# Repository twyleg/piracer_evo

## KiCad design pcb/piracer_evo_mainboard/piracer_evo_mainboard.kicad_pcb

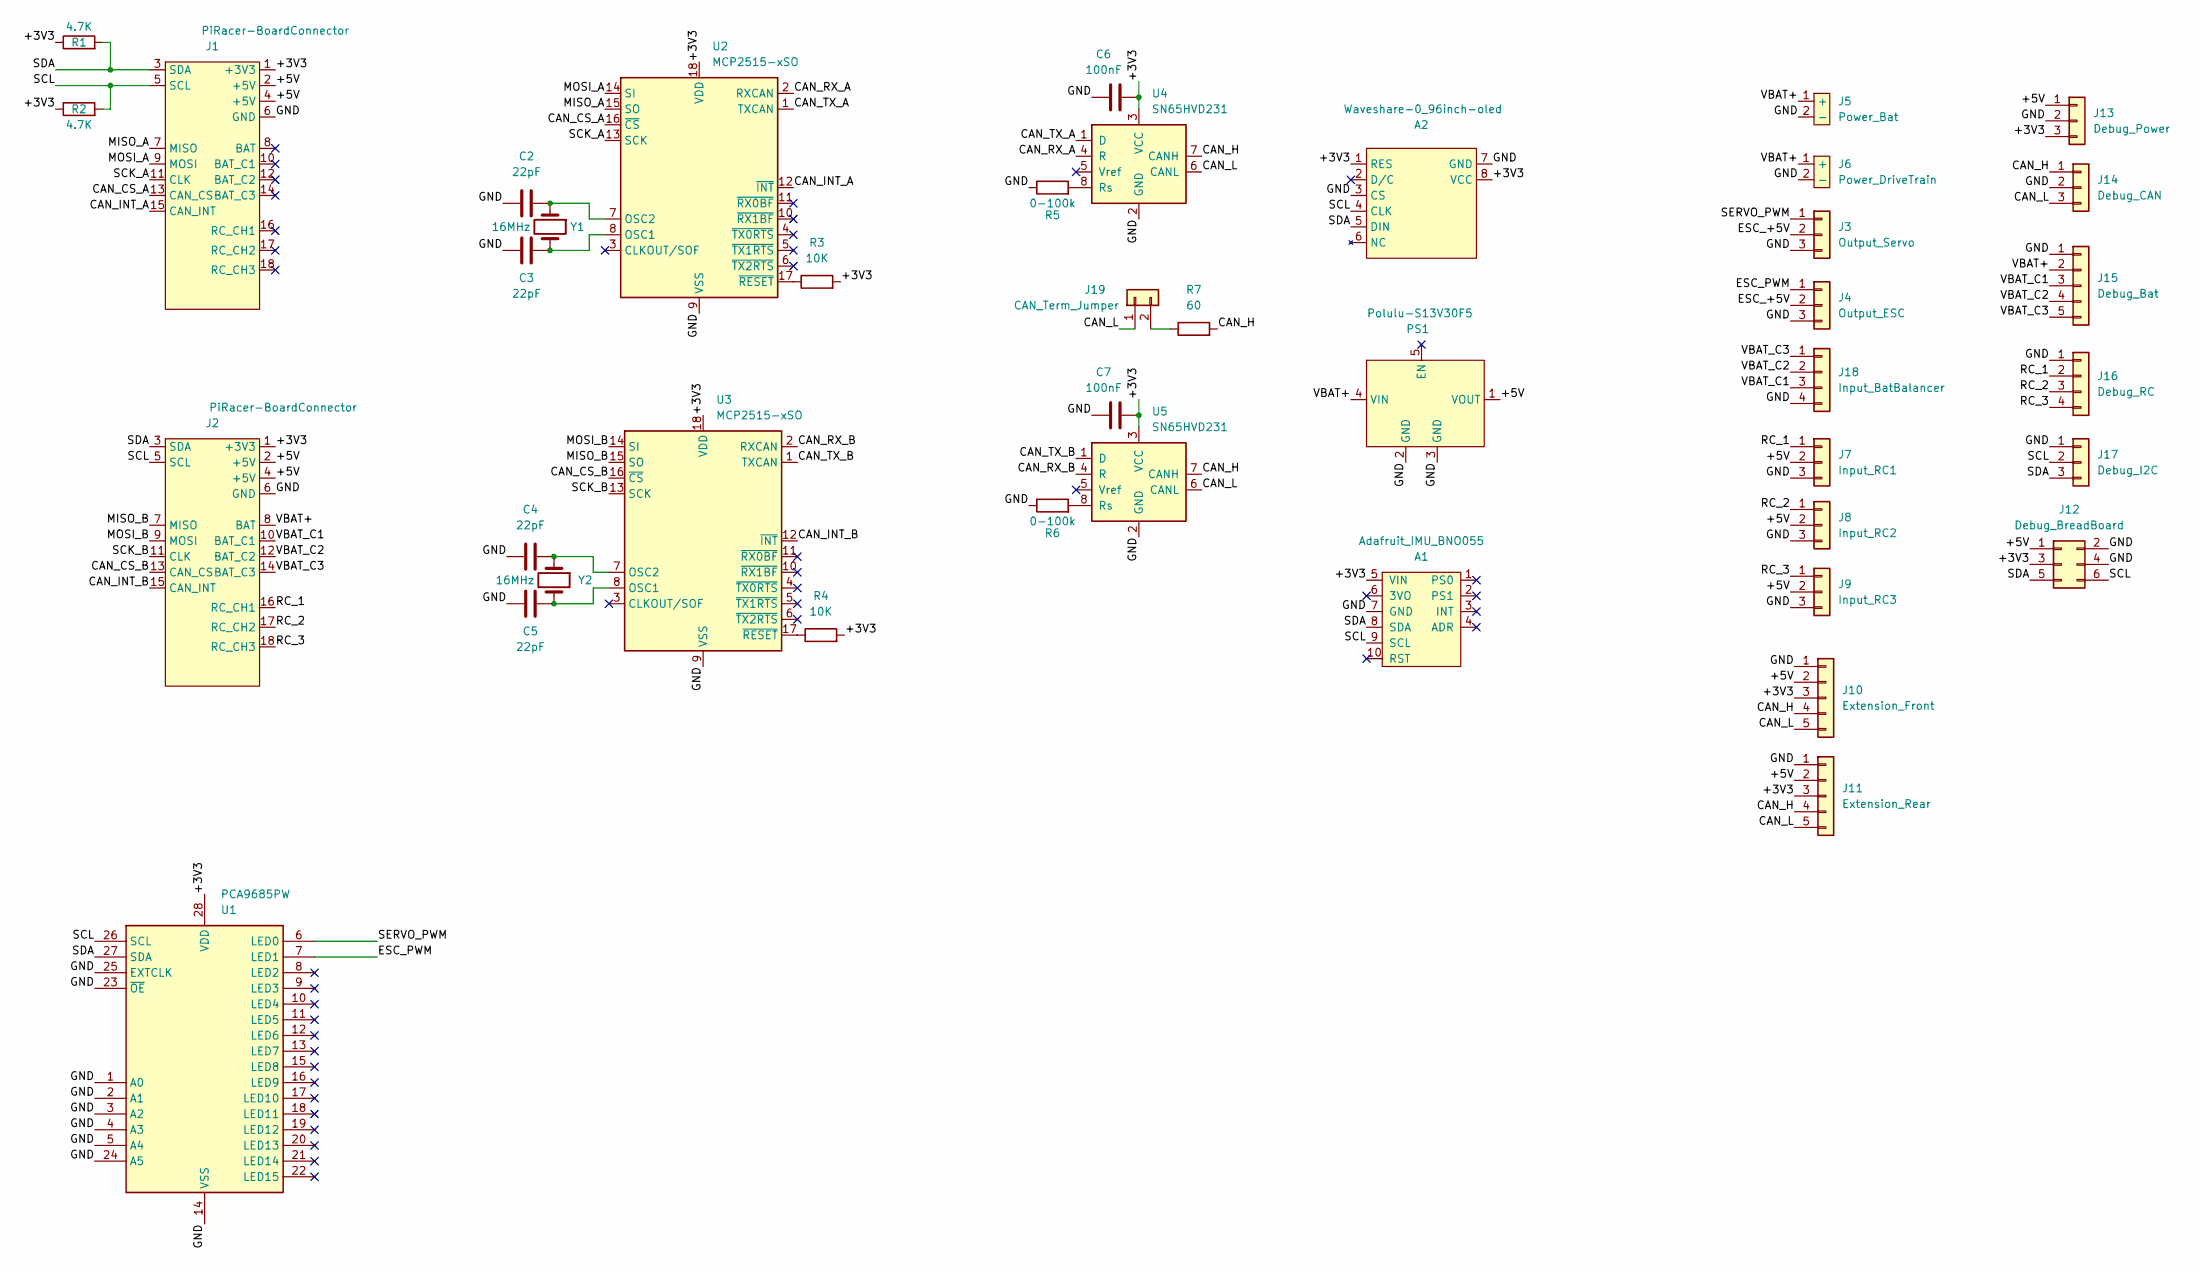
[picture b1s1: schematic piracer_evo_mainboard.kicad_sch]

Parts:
A1: Adafruit_IMU_BNO055
A2: Waveshare-0_96inch-oled
C2, C3, C4, C5: 22pF; C_0805_2012Metric_Pad1.18x1.45mm_HandSolder
C6, C7: 100nF; C_0805_2012Metric_Pad1.18x1.45mm_HandSolder
J1: PiRacer-BoardConnector; RaspberryPi3-ModelB-Power+I2C
J2: PiRacer-BoardConnector; Arduino_UNO_R3_WithMountingHoles-Power+I2C
J3: Output_Servo; PinHeader_1x03_P2.54mm_Vertical
J4: Output_ESC; PinHeader_1x03_P2.54mm_Vertical
J5: Power_Bat; T-Plug-Male
J6: Power_DriveTrain; T-Plug-Female
J7: Input_RC1; PinHeader_1x03_P2.54mm_Vertical
J8: Input_RC2; PinHeader_1x03_P2.54mm_Vertical
J9: Input_RC3; PinHeader_1x03_P2.54mm_Vertical
J10: Extension_Front; JST_EH_S5B-EH_1x05_P2.50mm_Horizontal
J11: Extension_Rear; JST_EH_S5B-EH_1x05_P2.50mm_Horizontal
J12: Debug_BreadBoard; PinHeader_2x03_P2.54mm_Vertical
J13: Debug_Power; PinHeader_1x03_P2.54mm_Horizontal
J14: Debug_CAN; PinHeader_1x03_P2.54mm_Horizontal
J15: Debug_Bat; PinHeader_1x05_P2.54mm_Horizontal
J16: Debug_RC; PinHeader_1x04_P2.54mm_Horizontal
J17: Debug_I2C; PinHeader_1x03_P2.54mm_Horizontal
J18: Input_BatBalancer; JST_EH_B4B-EH-A_1x04_P2.50mm_Vertical
J19: CAN_Term_Jumper; PinHeader_1x02_P2.54mm_Vertical
PS1: Polulu-S13V30F5
R1, R2: 4.7K; R_1206_3216Metric_Pad1.30x1.75mm_HandSolder
R3, R4: 10K; R_1206_3216Metric_Pad1.30x1.75mm_HandSolder
R5, R6: 0-100k; R_1206_3216Metric_Pad1.30x1.75mm_HandSolder
R7: 60; R_1206_3216Metric_Pad1.30x1.75mm_HandSolder
U1: PCA9685PW; TSSOP-28_4.4x9.7mm_P0.65mm
U2, U3: MCP2515-xSO; SOIC-18W_7.5x11.6mm_P1.27mm
U4, U5: SN65HVD231; SOIC-8_3.9x4.9mm_P1.27mm
Y1, Y2: 16MHz; Crystal_HC18-U_Vertical

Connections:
/+3V3: A1.5 (VIN), A2.1 (RES), A2.8 (VCC), C6.2, C7.2, J1.1 (+3V3), J2.1 (+3V3), J10.3, J11.3, J12.3, J13.3, R1.1, R2.1, R3.2, R4.2, U1.28 (VDD), U2.18 (VDD), U3.18 (VDD), U4.3 (VCC), U5.3 (VCC)
/+5V: J1.2 (+5V), J1.4 (+5V), J2.2 (+5V), J2.4 (+5V), J7.2, J8.2, J9.2, J10.2, J11.2, J12.1, J13.1, PS1.1 (VOUT)
/CAN_CS_A: J1.13 (CAN_CS), U2.16 (~CS)
/CAN_CS_B: J2.13 (CAN_CS), U3.16 (~CS)
/CAN_H: J10.4, J11.4, J14.1, R7.2, U4.7 (CANH), U5.7 (CANH)
/CAN_INT_A: J1.15 (CAN_INT), U2.12 (~INT)
/CAN_INT_B: J2.15 (CAN_INT), U3.12 (~INT)
/CAN_L: J10.5, J11.5, J14.3, J19.1, U4.6 (CANL), U5.6 (CANL)
/CAN_RX_A: U2.2 (RXCAN), U4.4 (R)
/CAN_RX_B: U3.2 (RXCAN), U5.4 (R)
/CAN_TX_A: U2.1 (TXCAN), U4.1 (D)
/CAN_TX_B: U3.1 (TXCAN), U5.1 (D)
/ESC_+5V: J3.2, J4.2
/ESC_PWM: J4.1, U1.7 (LED1)
/GND: A1.7 (GND), A2.3 (CS), A2.7 (GND), C2.1, C3.1, C4.1, C5.1, C6.1, C7.1, J1.6 (GND), J2.6 (GND), J3.3, J4.3, J5.2 (-), J6.2 (-), J7.3, J8.3, J9.3, J10.1, J11.1, J12.2, J12.4, J13.2, J14.2, J15.1, J16.1, J17.1, J18.4, PS1.2 (GND), PS1.3 (GND), R5.1, R6.1, U1.1 (A0), U1.2 (A1), U1.3 (A2), U1.4 (A3), U1.5 (A4), U1.14 (VSS), U1.23 (~OE), U1.24 (A5), U1.25 (EXTCLK), U2.9 (VSS), U3.9 (VSS), U4.2 (GND), U5.2 (GND)
/MISO_A: J1.7 (MISO), U2.15 (SO)
/MISO_B: J2.7 (MISO), U3.15 (SO)
/MOSI_A: J1.9 (MOSI), U2.14 (SI)
/MOSI_B: J2.9 (MOSI), U3.14 (SI)
/RC_1: J2.16 (RC_CH1), J7.1, J16.2
/RC_2: J2.17 (RC_CH2), J8.1, J16.3
/RC_3: J2.18 (RC_CH3), J9.1, J16.4
/SCK_A: J1.11 (CLK), U2.13 (SCK)
/SCK_B: J2.11 (CLK), U3.13 (SCK)
/SCL: A1.9 (SCL), A2.4 (CLK), J1.5 (SCL), J2.5 (SCL), J12.6, J17.2, R2.2, U1.26 (SCL)
/SDA: A1.8 (SDA), A2.5 (DIN), J1.3 (SDA), J2.3 (SDA), J12.5, J17.3, R1.2, U1.27 (SDA)
/SERVO_PWM: J3.1, U1.6 (LED0)
/VBAT+: J2.8 (BAT), J5.1 (+), J6.1 (+), J15.2, PS1.4 (VIN)
/VBAT_C1: J2.10 (BAT_C1), J15.3, J18.3
/VBAT_C2: J2.12 (BAT_C2), J15.4, J18.2
/VBAT_C3: J2.14 (BAT_C3), J15.5, J18.1
unnamed: C2.2, U2.7 (OSC2), Y1.1
unnamed: C3.2, U2.8 (OSC1), Y1.2
unnamed: C4.2, U3.7 (OSC2), Y2.1
unnamed: C5.2, U3.8 (OSC1), Y2.2
unnamed: R3.1, U2.17 (~RESET)
unnamed: R4.1, U3.17 (~RESET)
unnamed: R5.2, U4.8 (Rs)
unnamed: R6.2, U5.8 (Rs)
unnamed: J19.2, R7.1

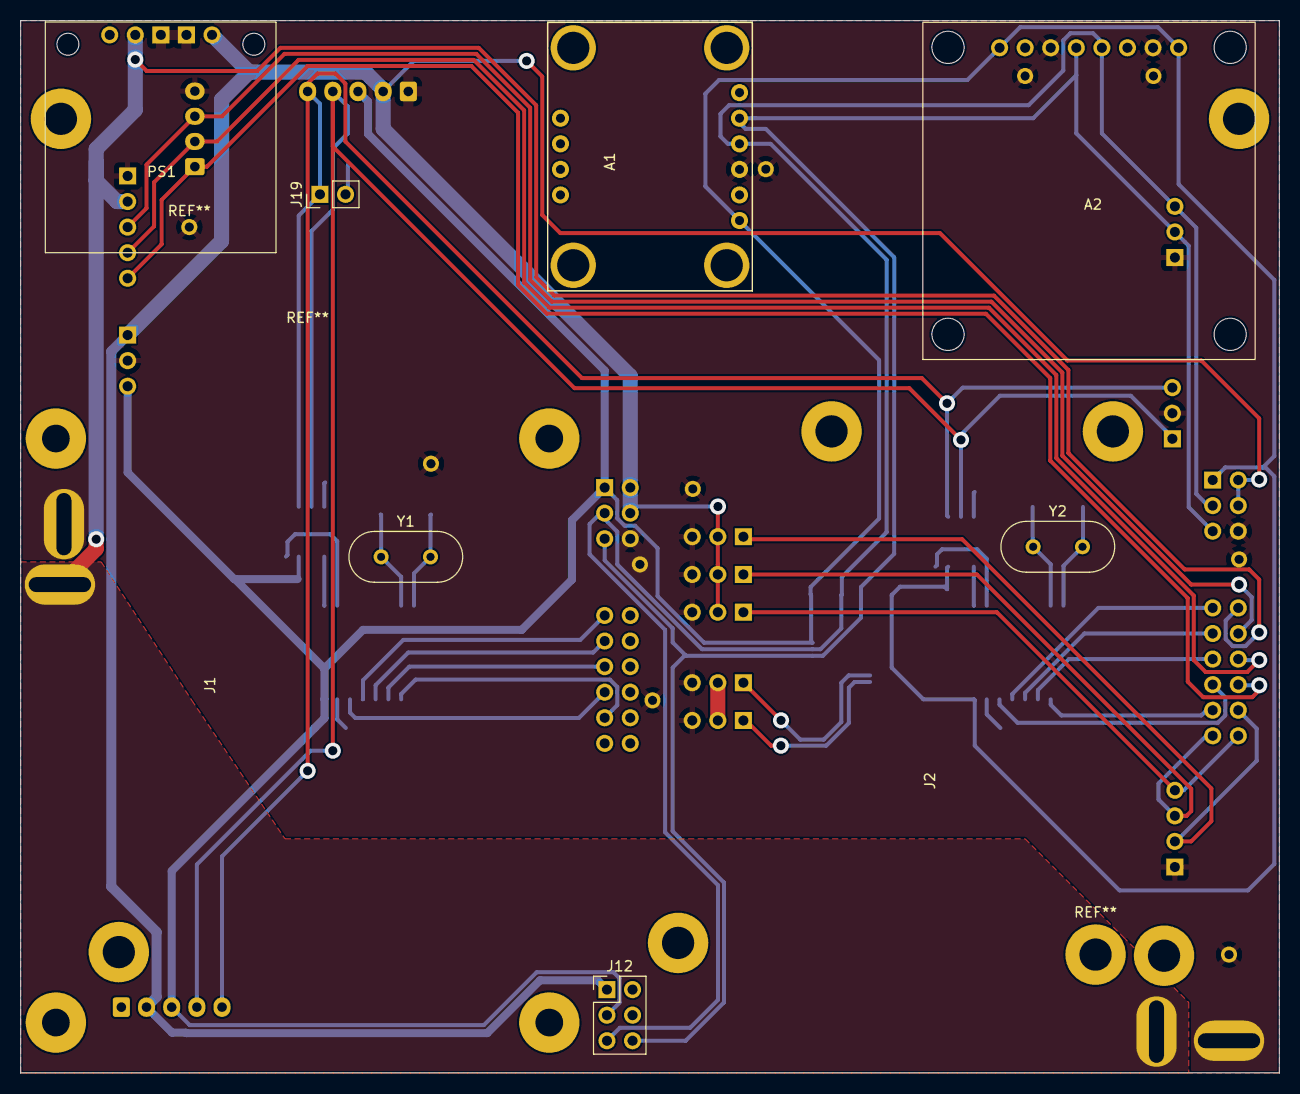
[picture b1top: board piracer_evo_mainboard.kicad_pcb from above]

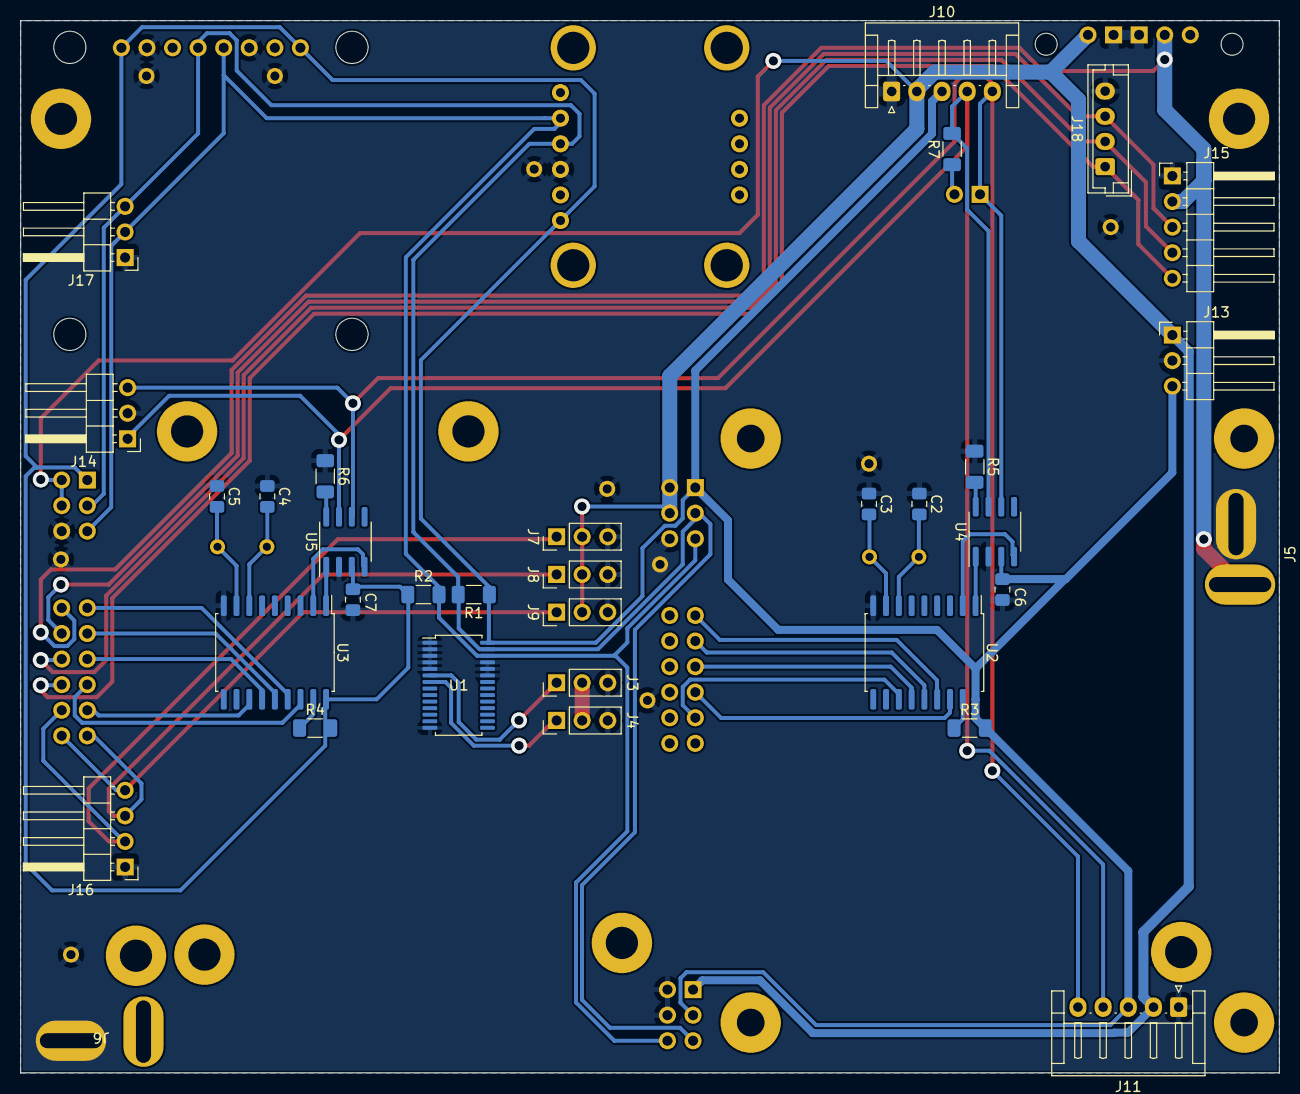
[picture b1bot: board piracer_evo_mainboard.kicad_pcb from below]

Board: 2 copper layers, 125.0 x 104.5 mm, 42 parts (33 on the bottom side), 40 nets.

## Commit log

2023-01-08 90% complete version
2023-01-15 First complete version
